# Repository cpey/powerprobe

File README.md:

# powerprobe

This board is intended to support side-channel analysis. It powers the target device and provides 20x amplification of the signal measured across a low-side shunt resistor.
 
See the [schematic](https://github.com/cpey/powerprobe/blob/main/images/powerprobe.pdf) for additional details.

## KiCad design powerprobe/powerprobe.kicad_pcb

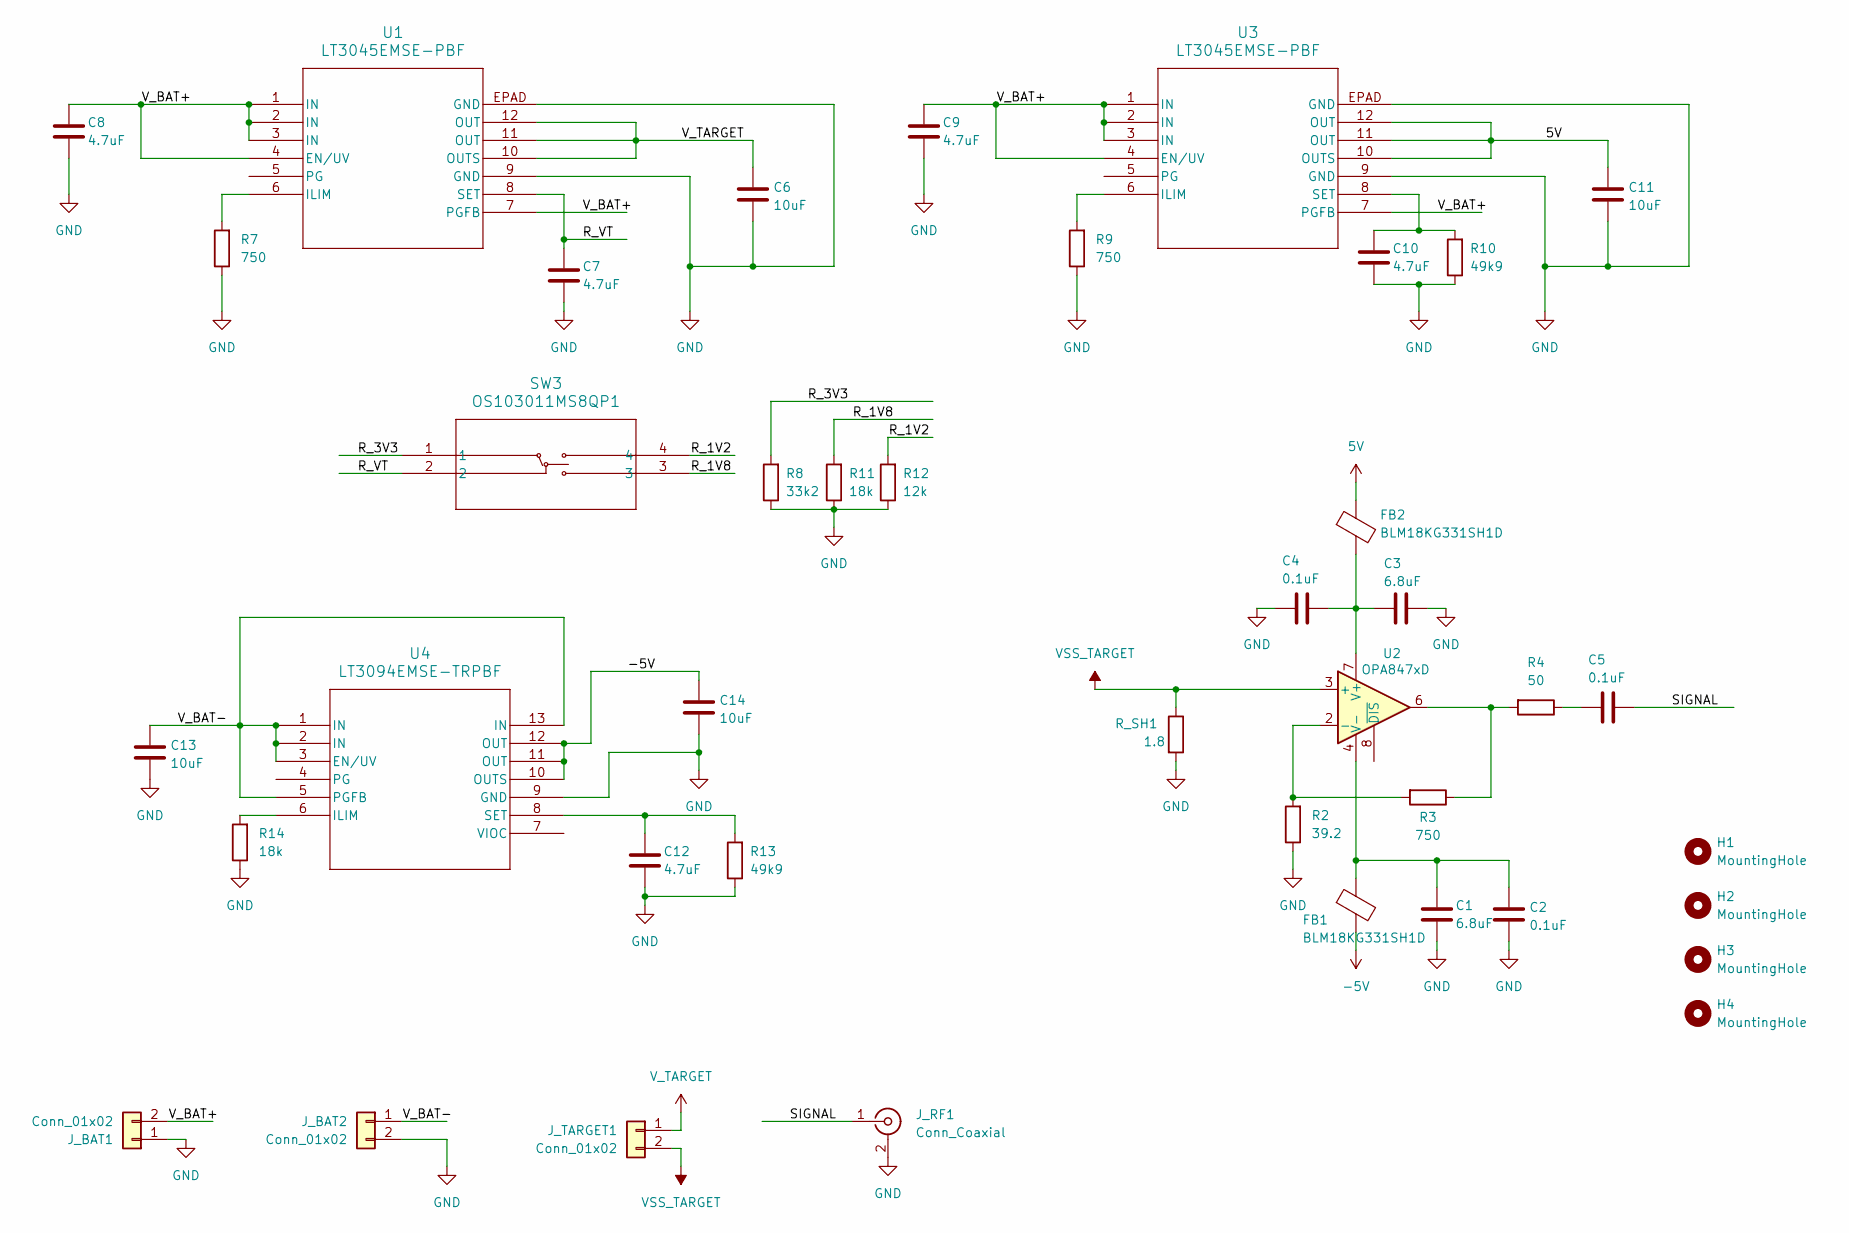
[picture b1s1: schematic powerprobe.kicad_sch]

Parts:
C1, C3: 6.8uF; C_0805_2012Metric
C2, C4, C5: 0.1uF; C_0805_2012Metric
C6, C11, C13, C14: 10uF; C_1206_3216Metric_Pad1.33x1.80mm_HandSolder
C7, C8, C9, C10, C12: 4.7uF; C_0805_2012Metric
FB1, FB2: BLM18KG331SH1D; BEADC1608X95N
H1, H2, H3, H4: MountingHole; MountingHole_3.2mm_M3_Pad_TopBottom
J_BAT1, J_BAT2: Conn_01x02; AMASS_XT30UPB-M_1x02_P5.0mm_Vertical
J_RF1: Conn_Coaxial; SMA_Molex_73251-1153_EdgeMount_Horizontal
J_TARGET1: Conn_01x02; CONN_1984617_PXC
R2: 39.2; R_0805_2012Metric
R3, R7, R9: 750; R_0805_2012Metric
R4: 50; R_0805_2012Metric
R8: 33k2; R_0805_2012Metric
R10, R13: 49k9; R_0805_2012Metric
R11, R14: 18k; R_0805_2012Metric
R12: 12k; R_0805_2012Metric
R_SH1: 1.8; R_0805_2012Metric
SW3: OS103011MS8QP1; DIP4_SP3T-TOP_4P3X8P6_CNK
U1, U3: LT3045EMSE-PBF; MSOP12_MSE_ADI
U2: OPA847xD; SOIC-8_3.9x4.9mm_P1.27mm
U4: LT3094EMSE-TRPBF; MSE_05-08-1666_ADI

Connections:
5V: C11.2, FB2.1, U3.10 (OUTS), U3.11 (OUT), U3.12 (OUT)
-5V: C14.2, FB1.2, U4.10 (OUTS), U4.11 (OUT), U4.12 (OUT)
/R_1V2: R12.2, SW3.4
/R_1V8: R11.2, SW3.3
/R_3V3: R8.2, SW3.1
/R_VT: C7.2, SW3.2, U1.8 (SET)
/SIGNAL: C5.1, J_RF1.1 (In)
/V_BAT+: C8.2, C9.2, J_BAT1.2, U1.1 (IN), U1.2 (IN), U1.3 (IN), U1.4 (EN/UV), U1.7 (PGFB), U3.1 (IN), U3.2 (IN), U3.3 (IN), U3.4 (EN/UV), U3.7 (PGFB)
/V_BAT-: C13.2, J_BAT2.1, U4.1 (IN), U4.2 (IN), U4.3 (EN/UV), U4.5 (PGFB), U4.13 (IN)
GND: C1.1, C2.1, C3.1, C4.2, C6.1, C7.1, C8.1, C9.1, C10.1, C11.1, C12.1, C13.1, C14.1, J_BAT1.1, J_BAT2.2, J_RF1.2 (Ext), R2.1, R7.1, R8.1, R9.1, R10.1, R11.1, R12.1, R13.1, R14.1, R_SH1.2, U1.9 (GND), U1.EPAD (GND), U3.9 (GND), U3.EPAD (GND), U4.9 (GND)
unnamed: C5.2, R4.1
unnamed: R3.1, R4.2, U2.6
unnamed: R7.2, U1.6 (ILIM)
unnamed: R2.2, R3.2, U2.2 (-)
unnamed: C3.2, C4.1, FB2.2, U2.7 (V+)
unnamed: C1.2, C2.2, FB1.1, U2.4 (V-)
unnamed: R9.2, U3.6 (ILIM)
unnamed: C10.2, R10.2, U3.8 (SET)
unnamed: R14.2, U4.6 (ILIM)
unnamed: C12.2, R13.2, U4.8 (SET)
VSS_TARGET: J_TARGET1.2, R_SH1.1, U2.3 (+)
V_TARGET: C6.2, J_TARGET1.1, U1.10 (OUTS), U1.11 (OUT), U1.12 (OUT)

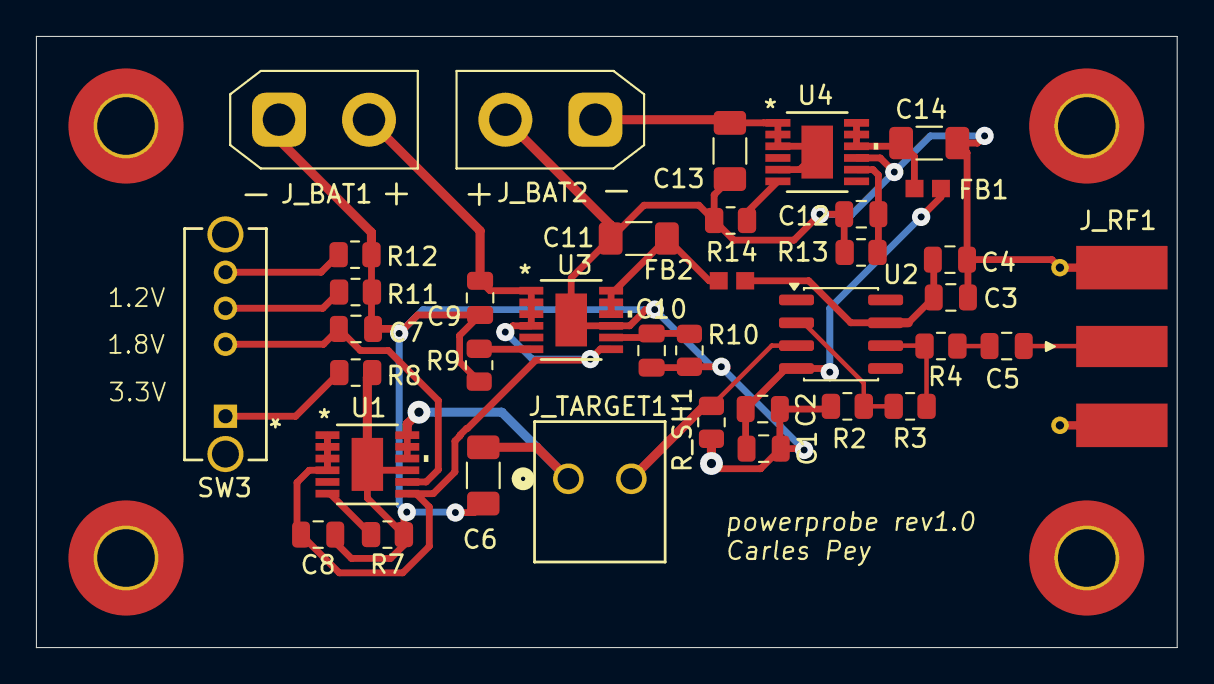
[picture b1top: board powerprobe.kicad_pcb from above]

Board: 2 copper layers, 63.4 x 34.0 mm, 41 parts (0 on the bottom side), 22 nets.

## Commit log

2026-05-31 Add project files
2026-06-01 Some more routing
2026-06-01 Board finished
2026-06-01 Add gerber files
2026-06-01 Updated title block details
2026-06-01 Update README file
2026-06-01 Add images
